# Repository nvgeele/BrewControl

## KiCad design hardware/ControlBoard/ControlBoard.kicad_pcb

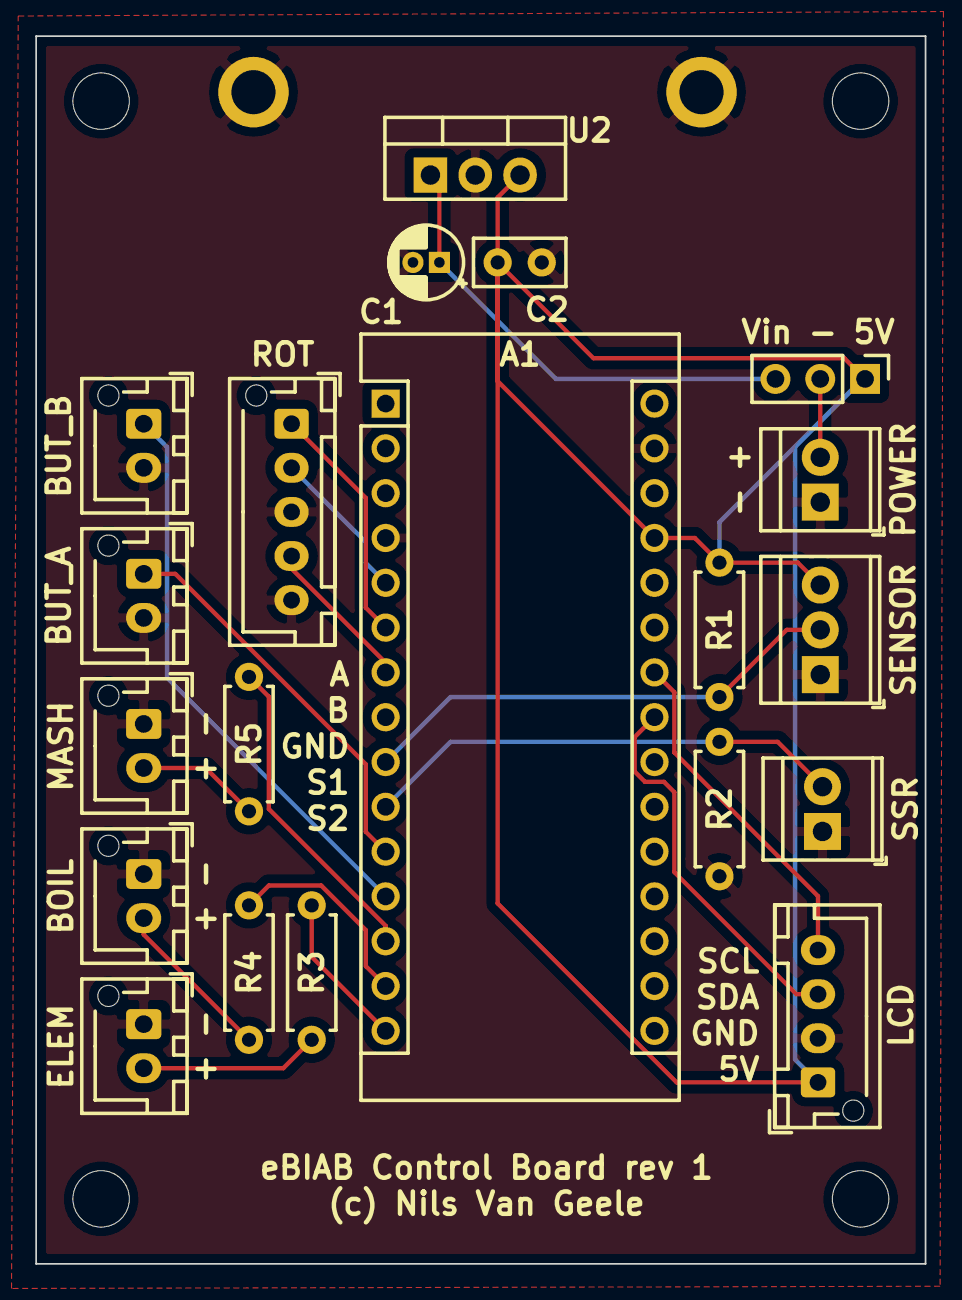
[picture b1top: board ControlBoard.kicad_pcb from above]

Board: 2 copper layers, 50.4 x 69.6 mm, 21 parts (0 on the bottom side), 19 nets.

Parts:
A1: Arduino_Nano_v3.x; Arduino_Nano
C1: 1u; CP_Radial_D4.0mm_P1.50mm
C2: 0.1u; C_Disc_D5.0mm_W2.5mm_P2.50mm
D1, D2, D3: LED; JST_XH_B2B-XH-AM_1x02_P2.50mm_Vertical
HS1: Heatsink_Pad_2Pin; Heatsink_Fischer_SK129-STS_42x25mm_2xDrill2.5mm
J1: Power; TerminalBlock_TE_282834-2_1x02_P2.54mm_Horizontal
J2: LCD; JST_XH_B4B-XH-AM_1x04_P2.50mm_Vertical
J3: SSR; TerminalBlock_TE_282834-2_1x02_P2.54mm_Horizontal
JP2: Jumper_NC_Dual; PinHeader_1x03_P2.54mm_Vertical
R1: 4k7; R_Axial_DIN0207_L6.3mm_D2.5mm_P7.62mm_Horizontal
R2: 10k; R_Axial_DIN0207_L6.3mm_D2.5mm_P7.62mm_Horizontal
R3, R4, R5: 330; R_Axial_DIN0207_L6.3mm_D2.5mm_P7.62mm_Horizontal
SW1: BUT_A; JST_XH_B2B-XH-AM_1x02_P2.50mm_Vertical
SW2: BUT_B; JST_XH_B2B-XH-AM_1x02_P2.50mm_Vertical
SW3: Rotary_Encoder_Switch; JST_XH_B5B-XH-AM_1x05_P2.50mm_Vertical
U1: DS18B20; TerminalBlock_TE_282834-3_1x03_P2.54mm_Horizontal
U2: LM7805_TO220; TO-220-3_Vertical

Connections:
+5V: A1.27, C2.1, J2.1, JP2.1, R1.1, U1.3, U2.3
GND: A1.4, A1.29, C1.2, C2.2, D1.1, D2.1, D3.1, HS1.1, J1.1, J2.2, J3.1, R2.1, SW1.2, SW2.2, SW3.C, SW3.S2, U1.1, U2.2
unnamed: A1.5, SW3.B
unnamed: A1.6, SW3.A
unnamed: A1.7, SW3.S1
unnamed: A1.9, R1.2, U1.2
unnamed: A1.10, J3.2, R2.2
unnamed: A1.11, SW1.1
unnamed: A1.12, SW2.1
unnamed: A1.13, R5.2
unnamed: A1.14, R4.2
unnamed: A1.15, R3.2
unnamed: A1.23, J2.3
unnamed: A1.24, J2.4
unnamed: C1.1, JP2.3, U2.1
unnamed: D1.2, R3.1
unnamed: D2.2, R4.1
unnamed: D3.2, R5.1
Vin: J1.2, JP2.2

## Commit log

2019-09-08 Initial commit, with code from instructables
2019-09-08 Added PID library as submodule
2019-09-08 Changed build settings to exclude examples folder
2019-09-08 Added autotune library, but not as submodule because of the structure of that git repo
2019-09-08 added all libraries and copied example code to main for test
2019-09-09 Swapped out wrong LCD library for the example
2019-09-09 changed lib again
2019-09-09 changed example so it compiles for future reference
2019-09-09 Clean slate
2020-05-07 Te lang gewacht met commits
2020-06-15 Set sensor resolution in set_up, re-enabled main loop and streamlined start menu
2020-06-15 Helpers for pre-mash confirmations, set SP method, start of mash method
2020-09-24 Updated submodules
2020-09-24 Environment for Nano and system test
2020-09-24 Moved pin definitions to header
2020-09-24 Moved button code to separate files
2020-09-24 Macro values for button presses
2020-09-24 Use BUT_OFF symbol for initial button state
2020-09-25 Some code to test wiring
2020-10-05 Dummy for calibration mode (serves as a reminder)
2021-03-01 Imported hardware stuff
2021-03-01 fix submodule (1)
2021-03-01 fix submodule (2)
2021-03-04 PCB cleanup
